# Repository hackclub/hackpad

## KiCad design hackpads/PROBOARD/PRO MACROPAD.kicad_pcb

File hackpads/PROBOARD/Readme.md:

# PROHACKBOARD
## My board is a simple and very much a standard macropad with 3 x 3 matrix with one encoder and one oled screen with xiao board and a case created in fusion 360

### Components
 . 9 switches
 . 1 encoder with switch
 . 1 oled 
 and in fusion 360 a backplate and joined main body and main plate with cavity for switches

 # images

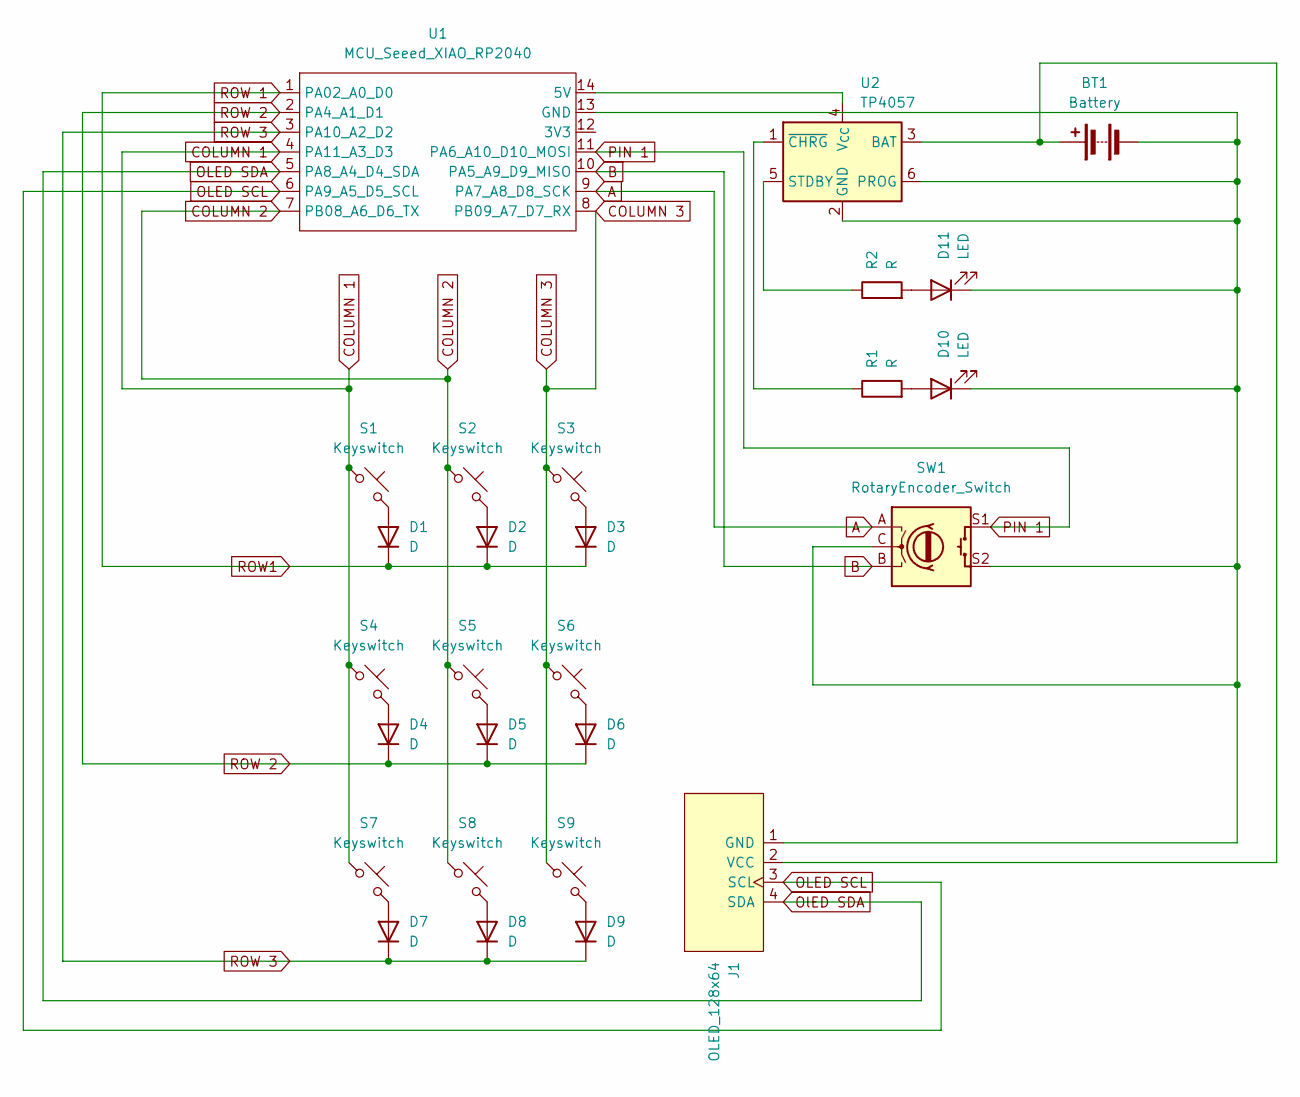
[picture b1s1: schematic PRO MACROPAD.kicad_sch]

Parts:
BT1: Battery; JST_PH_S2B-PH-K_1x02_P2.00mm_Horizontal
D1, D2, D3, D4, D5, D6, D7, D8, D9: D; Diode_SOD-123
D10, D11: LED; LED_D5.0mm
J1: OLED_128x64
R1, R2: R; Diode_SOD-123
S1, S2, S3, S4, S5, S6, S7, S8, S9: Keyswitch; Hotswap_MX_1.00u
SW1: RotaryEncoder_Switch; Encoder_EC11_MX_Combo
U1: MCU_Seeed_XIAO_RP2040; Seeed_XIAO_RP2040
U2: TP4057; TSOT-23-6

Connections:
A: SW1.A, U1.9 (PA7_A8_D8_SCK)
B: SW1.B, U1.10 (PA5_A9_D9_MISO)
COLUMN 1: S1.1, S4.1, S7.1, U1.4 (PA11_A3_D3)
COLUMN 2: S2.1, S5.1, S8.1, U1.7 (PB08_A6_D6_TX)
COLUMN 3: S3.1, S6.1, S9.1, U1.8 (PB09_A7_D7_RX)
unnamed: BT1.1 (+), J1.2 (VCC), U2.3 (BAT)
unnamed: BT1.2 (-), D10.1 (K), D11.1 (K), J1.1 (GND), SW1.C, SW1.S2, U1.13 (GND), U2.2 (GND), U2.6 (PROG)
unnamed: D1.2 (A), S1.2
unnamed: D2.2 (A), S2.2
unnamed: D3.2 (A), S3.2
unnamed: D4.2 (A), S4.2
unnamed: D5.2 (A), S5.2
unnamed: D6.2 (A), S6.2
unnamed: D7.2 (A), S7.2
unnamed: D8.2 (A), S8.2
unnamed: D9.2 (A), S9.2
unnamed: D10.2 (A), R1.2
unnamed: D11.2 (A), R2.2
unnamed: U1.14 (5V), U2.4 (V_{CC})
unnamed: R2.1, U2.5 (STDBY)
unnamed: R1.1, U2.1 (~CHRG)
OLED SCL: J1.3 (SCL), U1.6 (PA9_A5_D5_SCL)
OLED SDA: J1.4 (SDA), U1.5 (PA8_A4_D4_SDA)
PIN 1: SW1.S1, U1.11 (PA6_A10_D10_MOSI)
ROW 1: D1.1 (K), D2.1 (K), D3.1 (K), U1.1 (PA02_A0_D0)
ROW 2: D4.1 (K), D5.1 (K), D6.1 (K), U1.2 (PA4_A1_D1)
ROW 3: D7.1 (K), D8.1 (K), D9.1 (K), U1.3 (PA10_A2_D2)

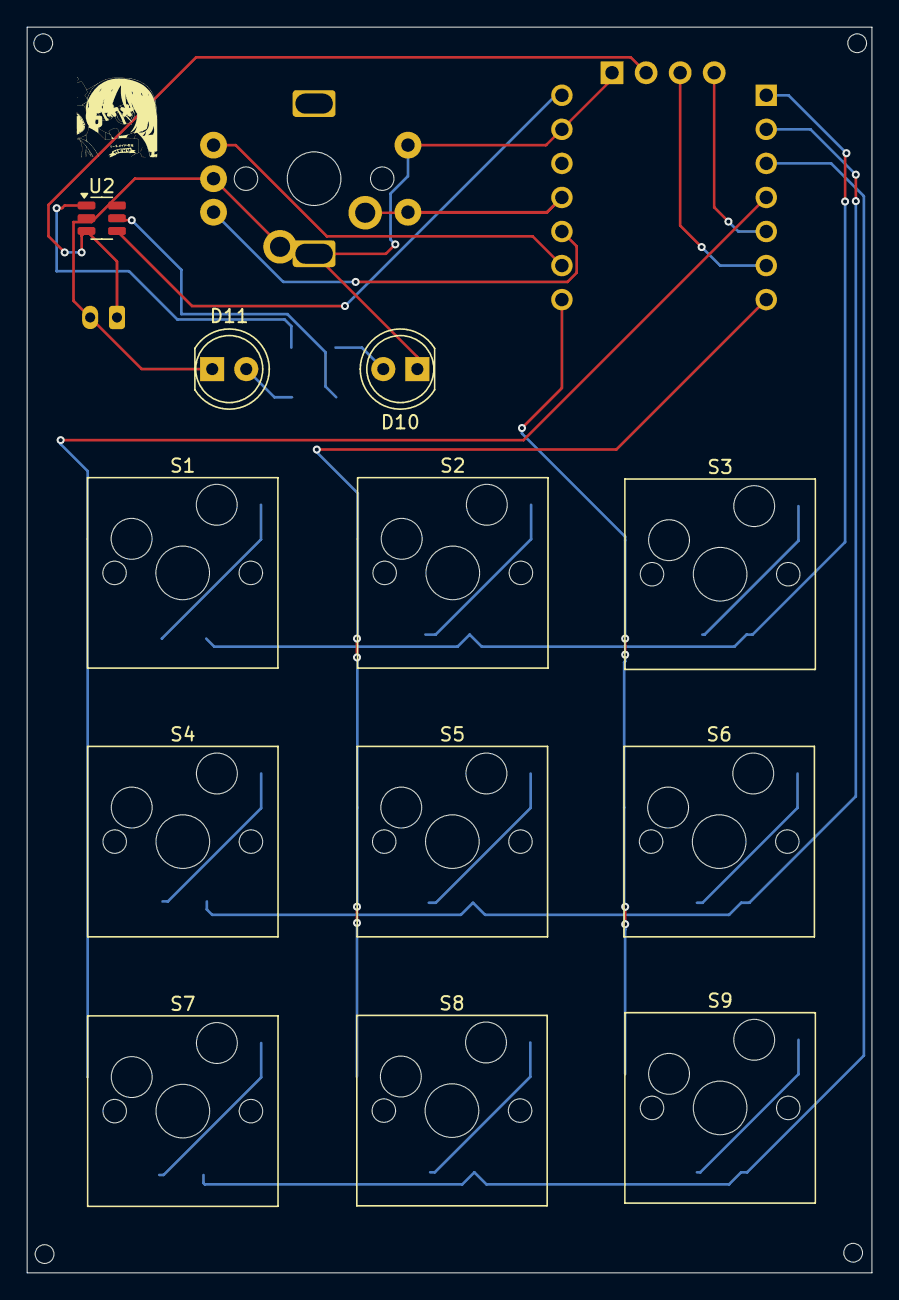
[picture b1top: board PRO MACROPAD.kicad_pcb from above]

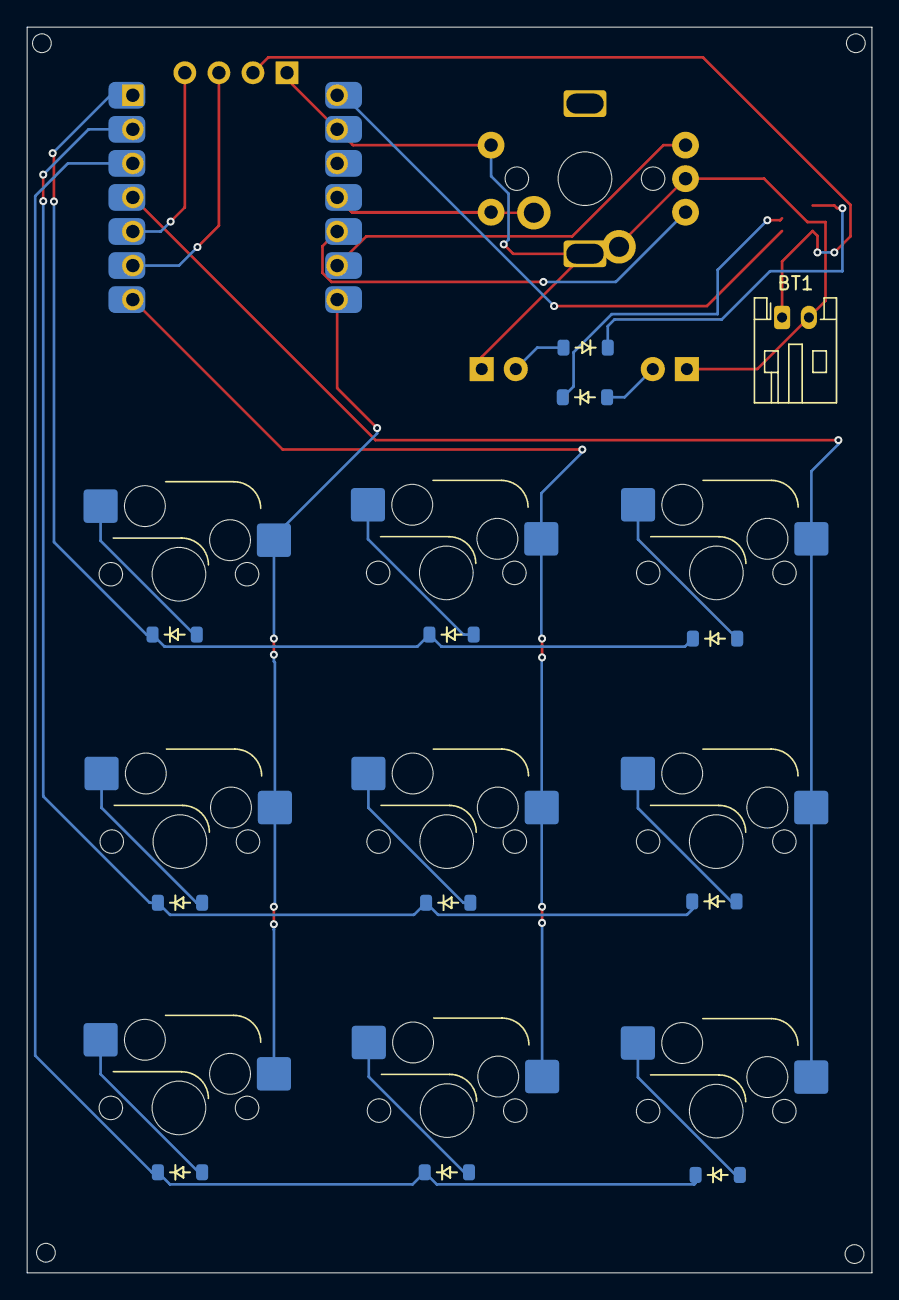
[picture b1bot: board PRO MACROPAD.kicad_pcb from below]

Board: 2 copper layers, 63.0 x 92.9 mm, 27 parts (13 on the bottom side), 27 nets.

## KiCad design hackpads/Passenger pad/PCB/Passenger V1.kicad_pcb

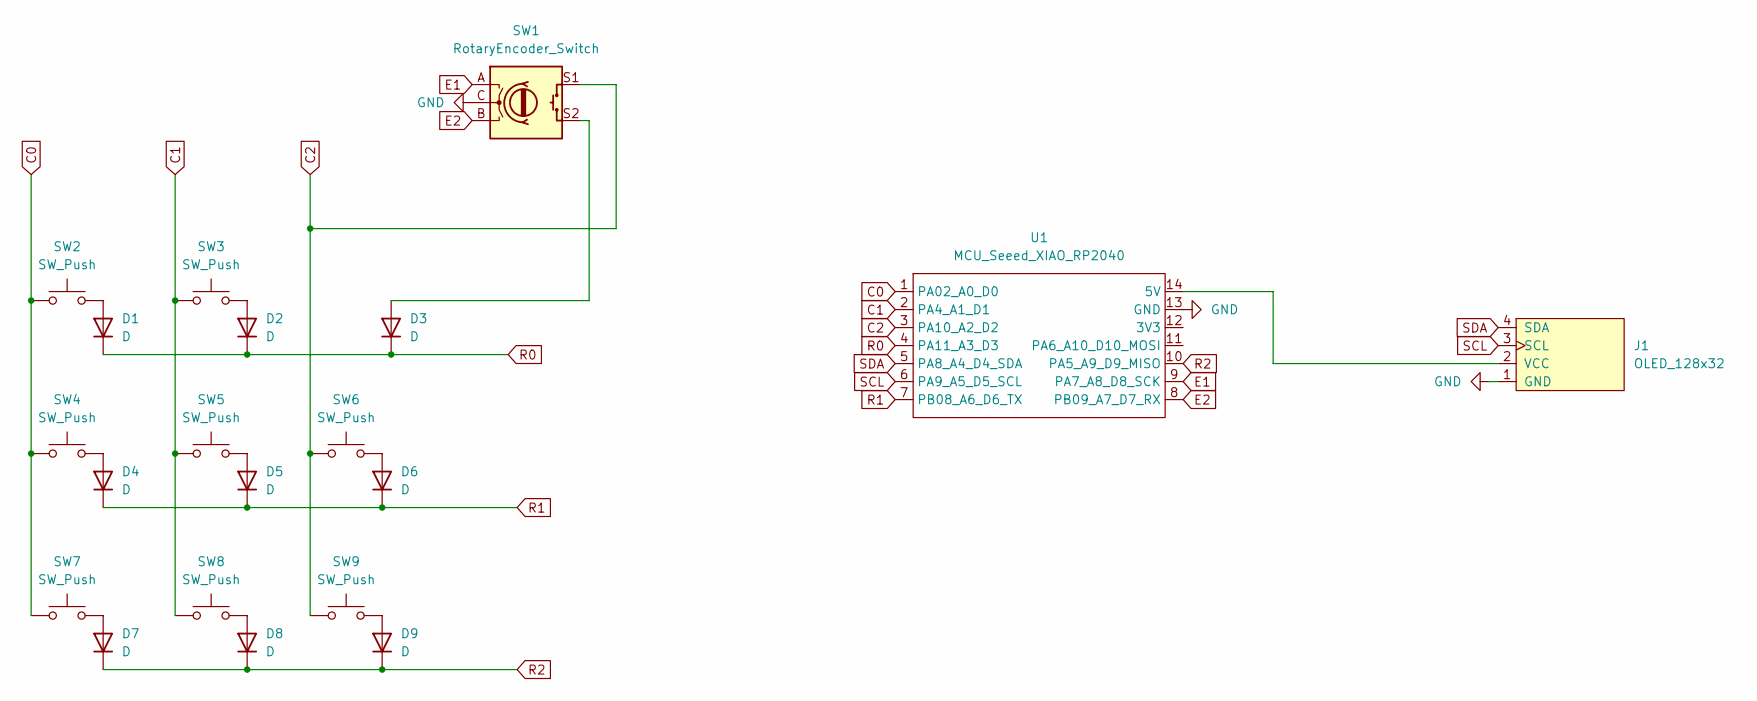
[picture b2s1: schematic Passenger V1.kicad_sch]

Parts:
D1, D2, D3, D4, D5, D6, D7, D8, D9: D; D_DO-35_SOD27_P7.62mm_Horizontal
J1: OLED_128x32; SSD1306-0.91-OLED-4pin-128x32 (2)
SW1: RotaryEncoder_Switch; RotaryEncoder_Alps_EC11E-Switch_Vertical_H20mm_CircularMoun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
SW2, SW3, SW4, SW5, SW6, SW7, SW8, SW9: SW_Push; SW_Cherry_MX_1.00u_PCB
U1: MCU_Seeed_XIAO_RP2040; XIAO-RP2040-DIP

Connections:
C0: SW2.1, SW4.1, SW7.1, U1.1 (PA02_A0_D0)
C1: SW3.1, SW5.1, SW8.1, U1.2 (PA4_A1_D1)
C2: SW1.S1, SW6.1, SW9.1, U1.3 (PA10_A2_D2)
E1: SW1.A, U1.9 (PA7_A8_D8_SCK)
E2: SW1.B, U1.8 (PB09_A7_D7_RX)
GND: J1.1 (GND), SW1.C, U1.13 (GND)
unnamed: D1.2 (A), SW2.2
unnamed: D2.2 (A), SW3.2
unnamed: D3.2 (A), SW1.S2
unnamed: D4.2 (A), SW4.2
unnamed: D5.2 (A), SW5.2
unnamed: D6.2 (A), SW6.2
unnamed: D7.2 (A), SW7.2
unnamed: D8.2 (A), SW8.2
unnamed: D9.2 (A), SW9.2
unnamed: J1.2 (VCC), U1.14 (5V)
R0: D1.1 (K), D2.1 (K), D3.1 (K), U1.4 (PA11_A3_D3)
R1: D4.1 (K), D5.1 (K), D6.1 (K), U1.7 (PB08_A6_D6_TX)
R2: D7.1 (K), D8.1 (K), D9.1 (K), U1.10 (PA5_A9_D9_MISO)
SCL: J1.3 (SCL), U1.6 (PA9_A5_D5_SCL)
SDA: J1.4 (SDA), U1.5 (PA8_A4_D4_SDA)

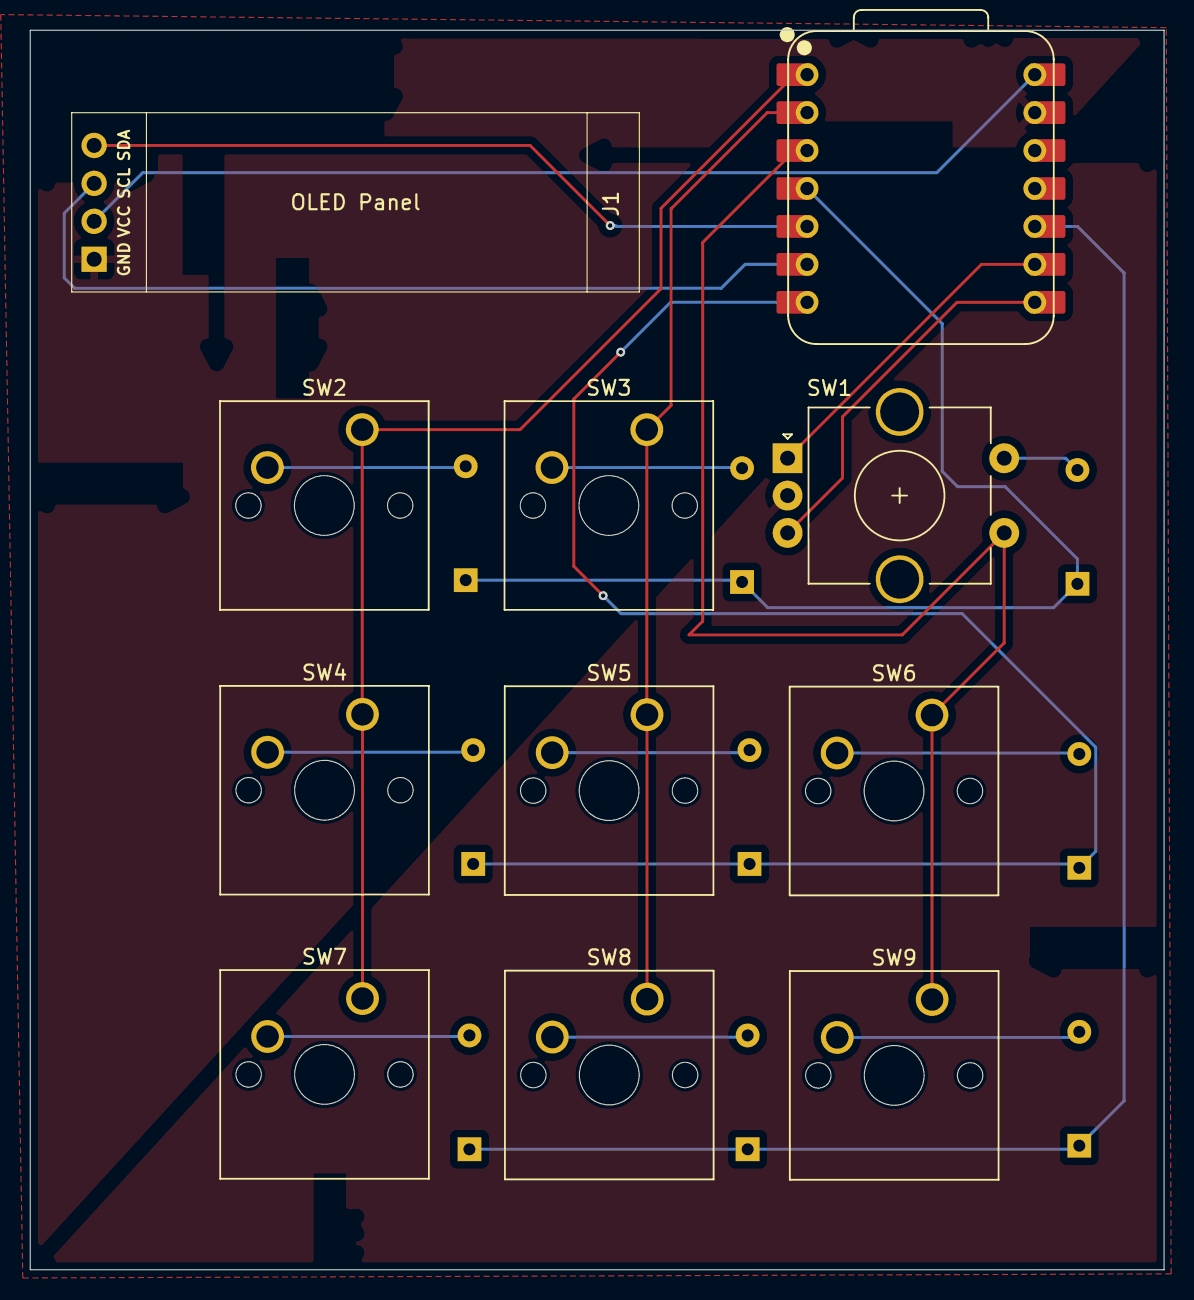
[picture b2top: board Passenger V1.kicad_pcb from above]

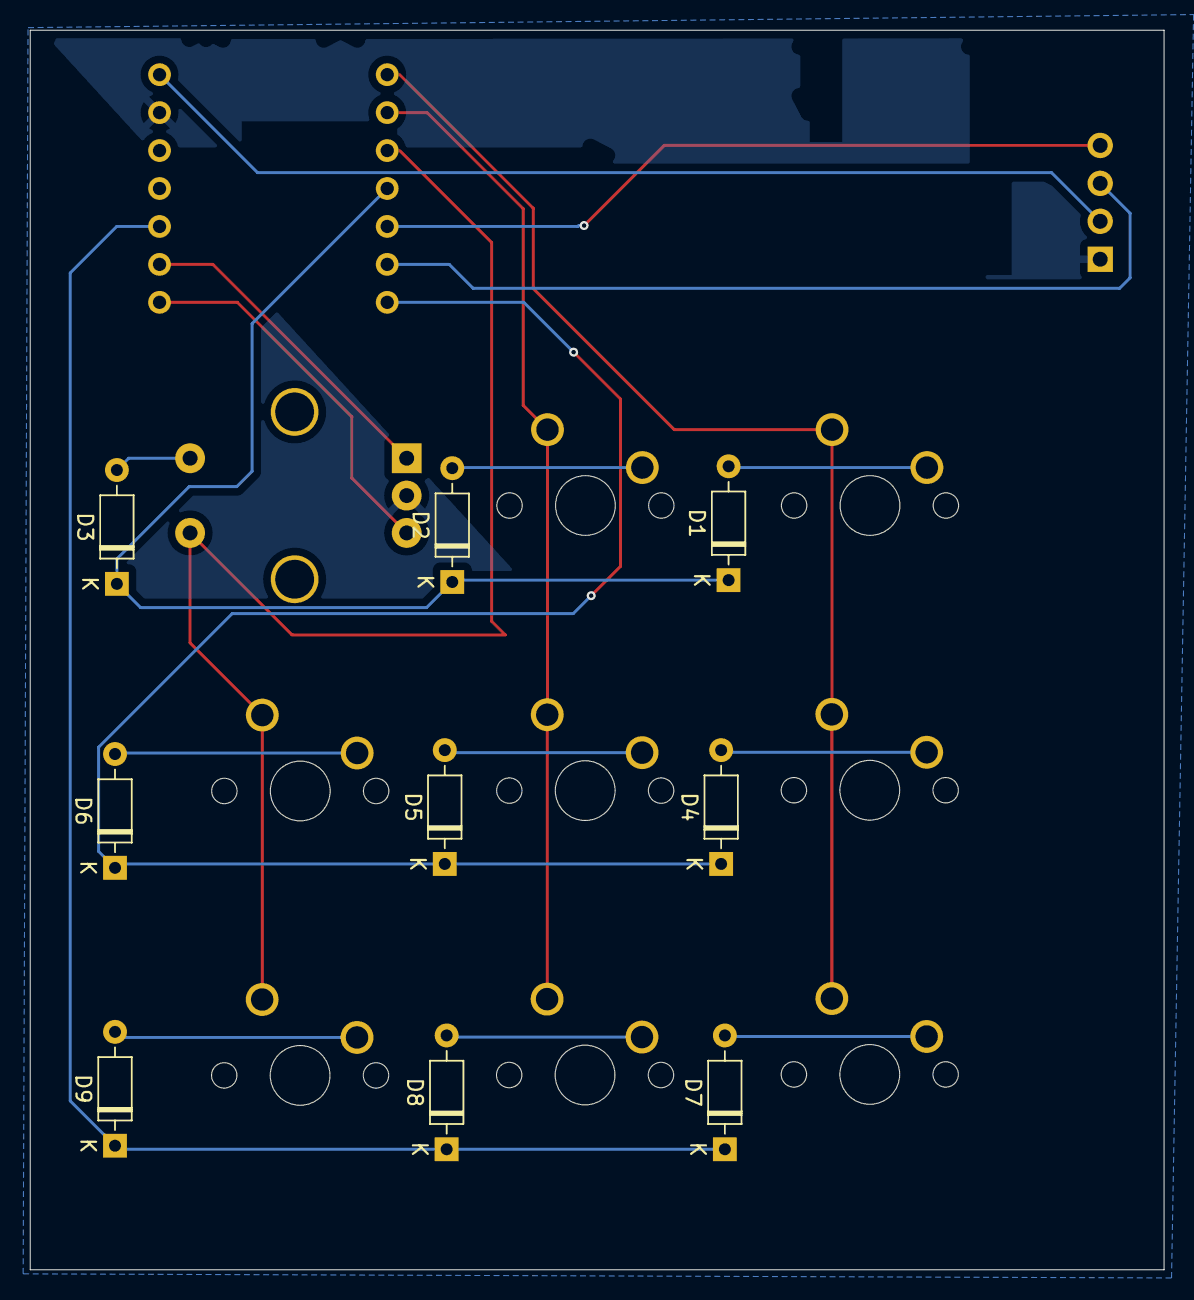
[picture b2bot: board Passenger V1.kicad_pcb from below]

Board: 2 copper layers, 75.9 x 83.0 mm, 20 parts (9 on the bottom side), 21 nets.

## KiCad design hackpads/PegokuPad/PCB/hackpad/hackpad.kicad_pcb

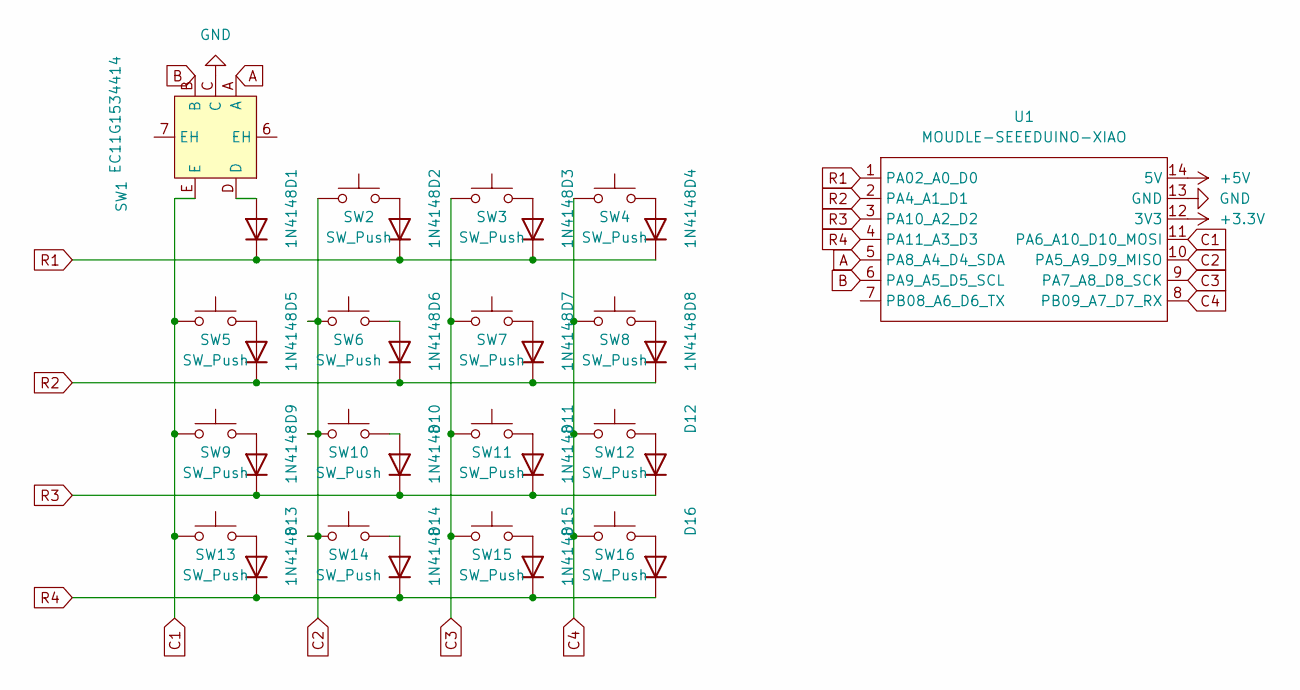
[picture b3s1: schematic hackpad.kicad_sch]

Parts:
D1, D2, D3, D4, D5, D6, D7, D8, D9, D10, D11, D12, D13, D14, D15, D16: 1N4148; D_DO-35_SOD27_P7.62mm_Horizontal
SW1: EC11G1534414; SW-TH_EC11G1534414; LCSC Part C1322547
SW2, SW3, SW4, SW5, SW6, SW7, SW8, SW9, SW10, SW11, SW12, SW13, SW14, SW15, SW16: SW_Push; SW_Cherry_MX_1.00u_PCB
U1: MOUDLE-SEEEDUINO-XIAO; XIAO-RP2040-DIP

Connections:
+3.3V: U1.12 (3V3)
+5V: U1.14 (5V)
A: SW1.A, U1.5 (PA8_A4_D4_SDA)
B: SW1.B, U1.6 (PA9_A5_D5_SCL)
C1: SW1.E, SW5.1, SW9.1, SW13.1, U1.11 (PA6_A10_D10_MOSI)
C2: SW2.1, SW6.1, SW10.1, SW14.1, U1.10 (PA5_A9_D9_MISO)
C3: SW3.1, SW7.1, SW11.1, SW15.1, U1.9 (PA7_A8_D8_SCK)
C4: SW4.1, SW8.1, SW12.1, SW16.1, U1.8 (PB09_A7_D7_RX)
GND: SW1.C, U1.13 (GND)
unnamed: D1.2 (A), SW1.D
unnamed: D2.2 (A), SW2.2
unnamed: D3.2 (A), SW3.2
unnamed: D4.2 (A), SW4.2
unnamed: D5.2 (A), SW5.2
unnamed: D6.2 (A), SW6.2
unnamed: D7.2 (A), SW7.2
unnamed: D8.2 (A), SW8.2
unnamed: D9.2 (A), SW9.2
unnamed: D10.2 (A), SW10.2
unnamed: D11.2 (A), SW11.2
unnamed: D12.2 (A), SW12.2
unnamed: D13.2 (A), SW13.2
unnamed: D14.2 (A), SW14.2
unnamed: D15.2 (A), SW15.2
unnamed: D16.2 (A), SW16.2
R1: D1.1 (K), D2.1 (K), D3.1 (K), D4.1 (K), U1.1 (PA02_A0_D0)
R2: D5.1 (K), D6.1 (K), D7.1 (K), D8.1 (K), U1.2 (PA4_A1_D1)
R3: D9.1 (K), D10.1 (K), D11.1 (K), D12.1 (K), U1.3 (PA10_A2_D2)
R4: D13.1 (K), D14.1 (K), D15.1 (K), D16.1 (K), U1.4 (PA11_A3_D3)

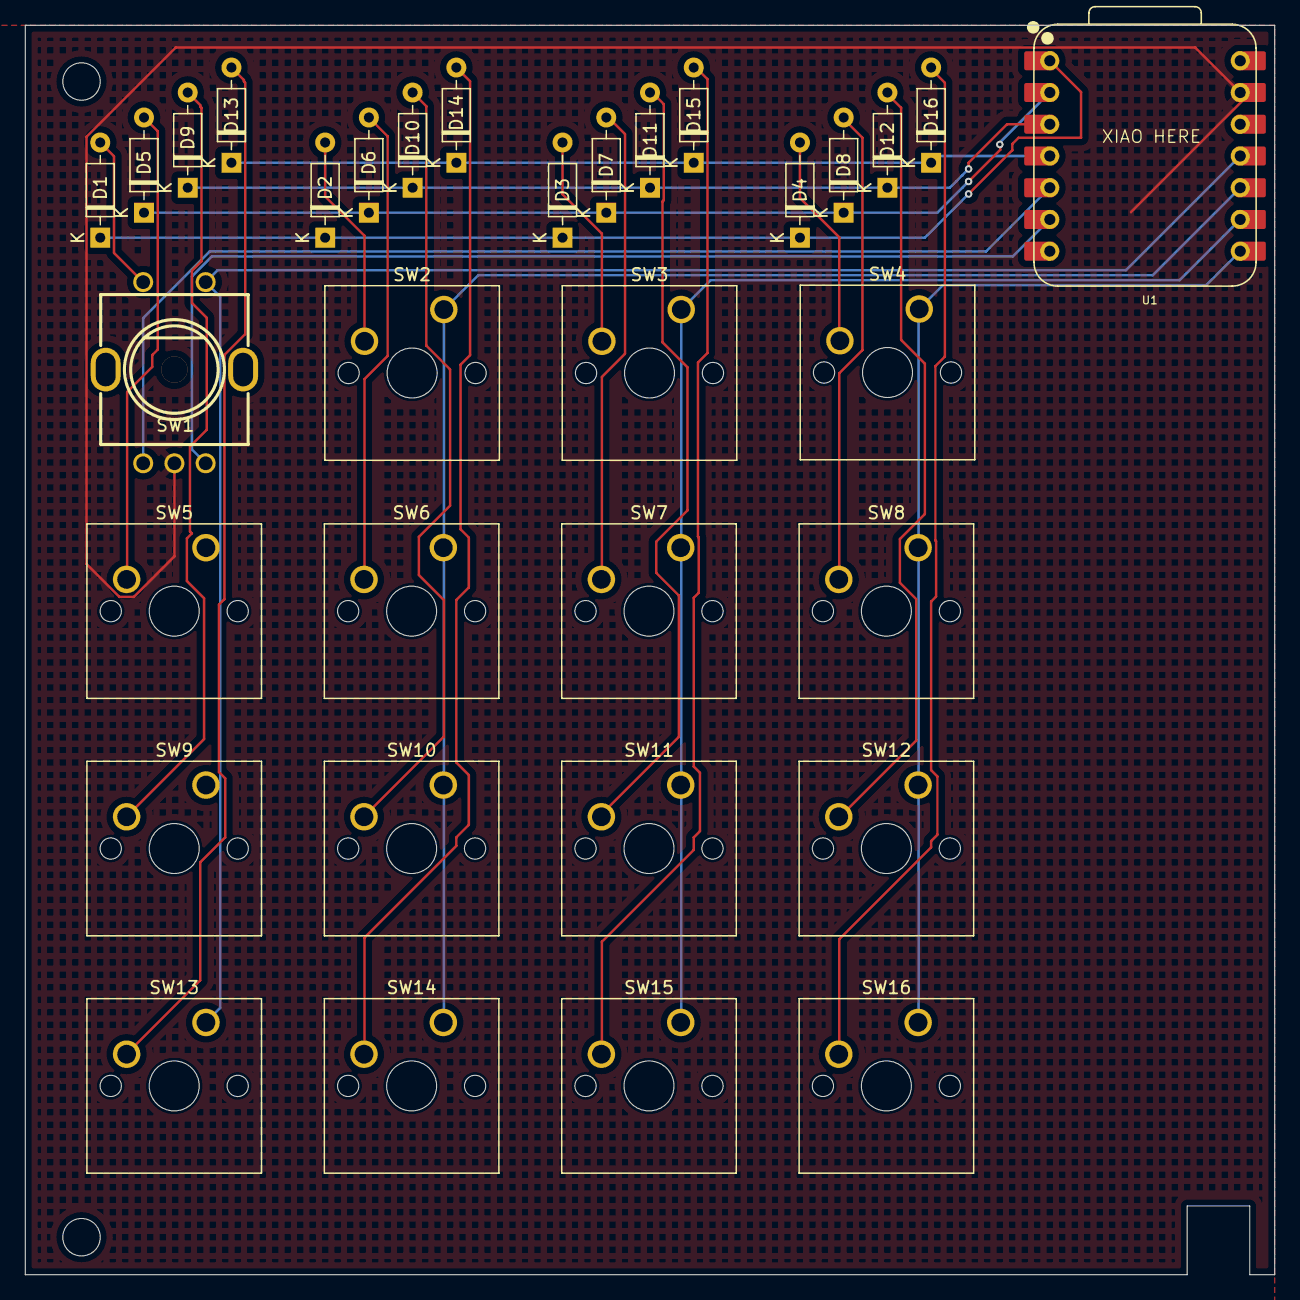
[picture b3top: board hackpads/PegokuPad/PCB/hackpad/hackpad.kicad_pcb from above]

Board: 2 copper layers, 100.0 x 100.0 mm, 33 parts (0 on the bottom side), 27 nets.

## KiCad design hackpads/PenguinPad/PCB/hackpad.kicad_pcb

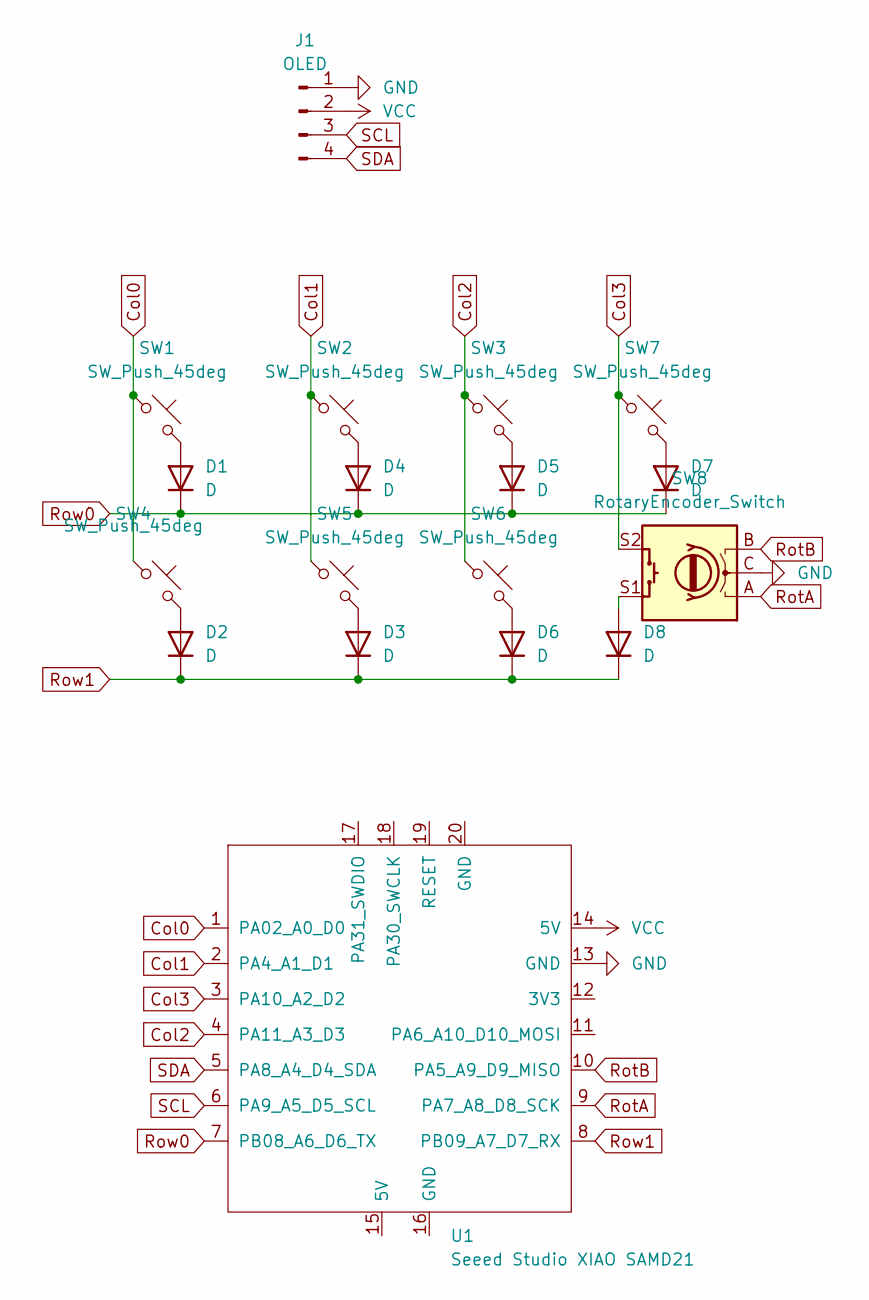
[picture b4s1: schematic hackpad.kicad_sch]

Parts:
D1, D2, D3, D4, D5, D6, D7, D8: D; D_DO-35_SOD27_P7.62mm_Horizontal
J1: OLED; SSD1306-0.91-OLED-4pin-128x32
SW1, SW2, SW3, SW4, SW5, SW6, SW7: SW_Push_45deg; SW_Cherry_MX_1.00u_PCB
SW8: RotaryEncoder_Switch; RotaryEncoder_Alps_EC11E-Switch_Vertical_H20mm
U1: Seeed Studio XIAO SAMD21; XIAO-Generic-Thruhole-14P-2.54-21X17.8MM

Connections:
Col0: SW1.1, SW4.1, U1.1 (PA02_A0_D0)
Col1: SW2.1, SW5.1, U1.2 (PA4_A1_D1)
Col2: SW3.1, SW6.1, U1.4 (PA11_A3_D3)
Col3: SW7.1, SW8.S2, U1.3 (PA10_A2_D2)
GND: J1.1, SW8.C, U1.13 (GND)
unnamed: D1.2 (A), SW1.2
unnamed: D2.2 (A), SW4.2
unnamed: D3.2 (A), SW5.2
unnamed: D4.2 (A), SW2.2
unnamed: D5.2 (A), SW3.2
unnamed: D6.2 (A), SW6.2
unnamed: D7.2 (A), SW7.2
unnamed: D8.2 (A), SW8.S1
RotA: SW8.A, U1.9 (PA7_A8_D8_SCK)
RotB: SW8.B, U1.10 (PA5_A9_D9_MISO)
Row0: D1.1 (K), D4.1 (K), D5.1 (K), D7.1 (K), U1.7 (PB08_A6_D6_TX)
Row1: D2.1 (K), D3.1 (K), D6.1 (K), D8.1 (K), U1.8 (PB09_A7_D7_RX)
SCL: J1.3, U1.6 (PA9_A5_D5_SCL)
SDA: J1.4, U1.5 (PA8_A4_D4_SDA)
VCC: J1.2, U1.14 (5V)

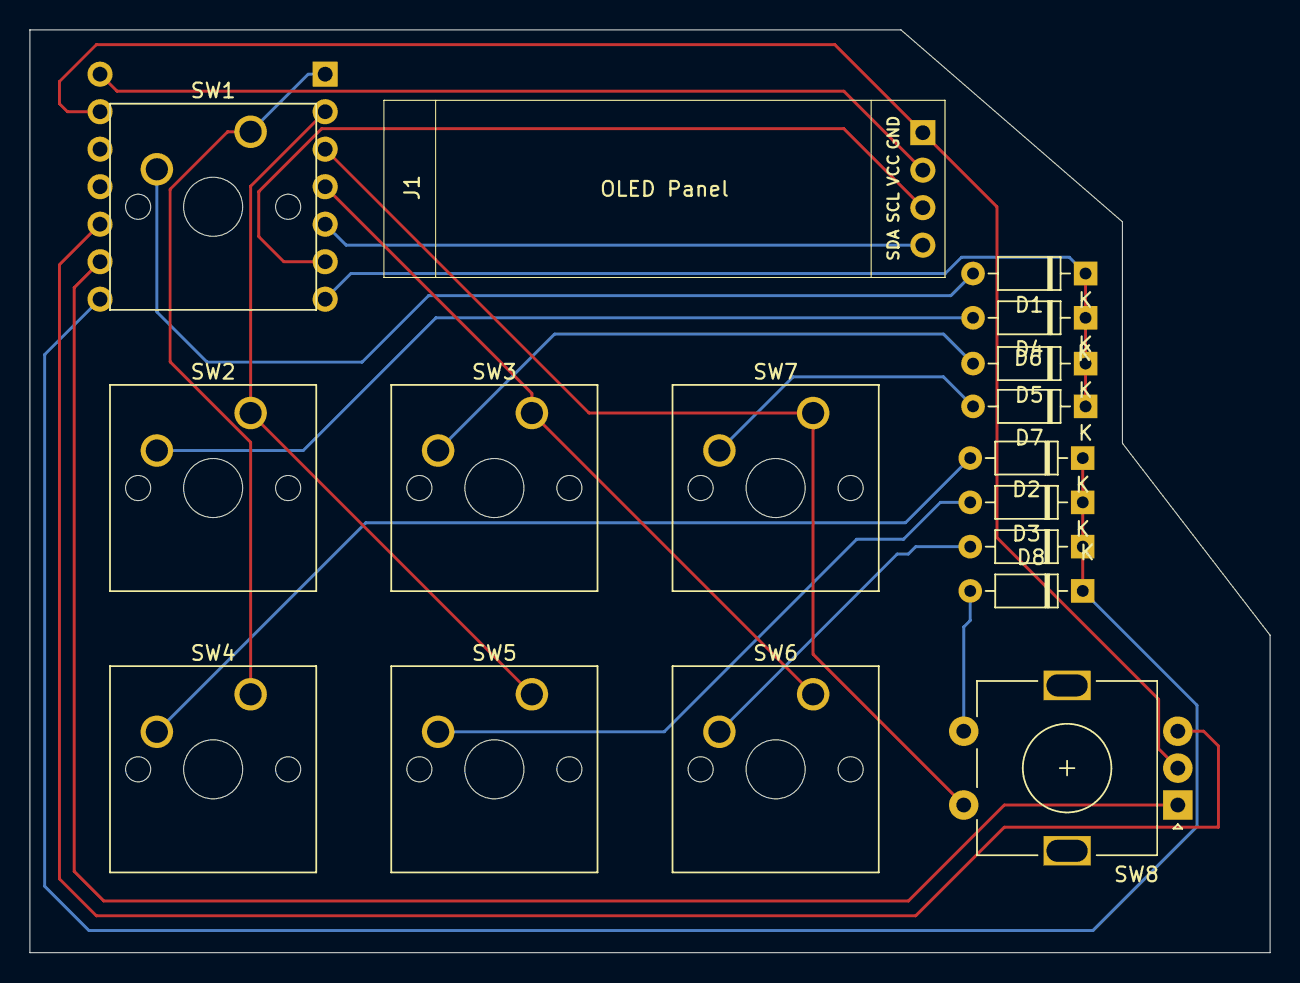
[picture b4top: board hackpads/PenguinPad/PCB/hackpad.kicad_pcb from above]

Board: 2 copper layers, 84.0 x 62.5 mm, 18 parts (1 on the bottom side), 20 nets.

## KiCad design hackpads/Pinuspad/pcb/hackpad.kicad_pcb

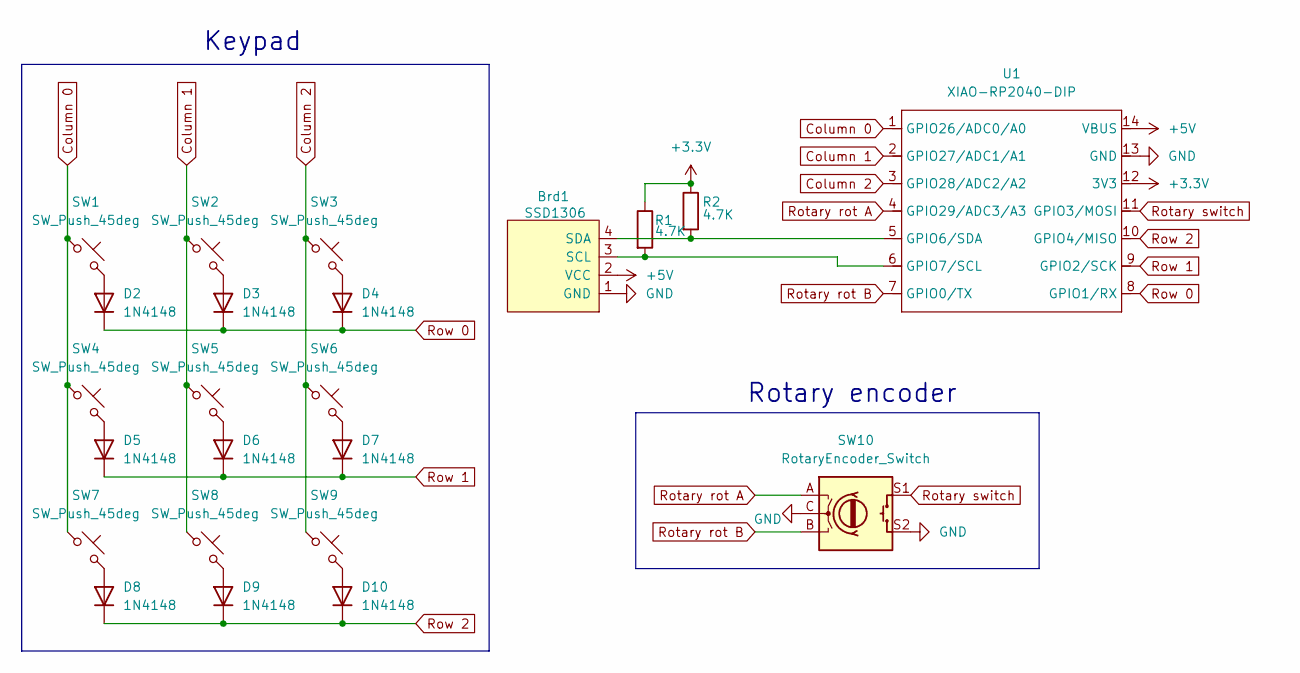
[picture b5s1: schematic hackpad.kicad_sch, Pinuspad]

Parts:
Brd1: SSD1306; 128x64OLED
D2, D3, D4, D5, D6, D7, D8, D9, D10: 1N4148; D_DO-35_SOD27_P7.62mm_Horizontal
R1, R2: 4.7K; R_Axial_DIN0204_L3.6mm_D1.6mm_P7.62mm_Horizontal
SW1, SW2, SW3, SW4, SW5, SW6, SW7, SW8, SW9: SW_Push_45deg; SW_Cherry_MX_1.00u_PCB
SW10: RotaryEncoder_Switch; RotaryEncoder_Alps_EC11E-Switch_Vertical_H20mm_CircularMoun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
U1: XIAO-RP2040-DIP

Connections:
+3.3V: R1.1, R2.1, U1.12 (3V3)
+5V: Brd1.2 (VCC), U1.14 (VBUS)
Column 0: SW1.1, SW4.1, SW7.1, U1.1 (GPIO26/ADC0/A0)
Column 1: SW2.1, SW5.1, SW8.1, U1.2 (GPIO27/ADC1/A1)
Column 2: SW3.1, SW6.1, SW9.1, U1.3 (GPIO28/ADC2/A2)
GND: Brd1.1 (GND), SW10.C, SW10.S2, U1.13 (GND)
unnamed: Brd1.3 (SCL), R1.2, U1.6 (GPIO7/SCL)
unnamed: Brd1.4 (SDA), R2.2, U1.5 (GPIO6/SDA)
unnamed: D2.2 (A), SW1.2
unnamed: D3.2 (A), SW2.2
unnamed: D4.2 (A), SW3.2
unnamed: D5.2 (A), SW4.2
unnamed: D6.2 (A), SW5.2
unnamed: D7.2 (A), SW6.2
unnamed: D8.2 (A), SW7.2
unnamed: D9.2 (A), SW8.2
unnamed: D10.2 (A), SW9.2
Rotary rot A: SW10.A, U1.4 (GPIO29/ADC3/A3)
Rotary rot B: SW10.B, U1.7 (GPIO0/TX)
Rotary switch: SW10.S1, U1.11 (GPIO3/MOSI)
Row 0: D2.1 (K), D3.1 (K), D4.1 (K), U1.8 (GPIO1/RX)
Row 1: D5.1 (K), D6.1 (K), D7.1 (K), U1.9 (GPIO2/SCK)
Row 2: D8.1 (K), D9.1 (K), D10.1 (K), U1.10 (GPIO4/MISO)

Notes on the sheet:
Rotary encoder
Keypad

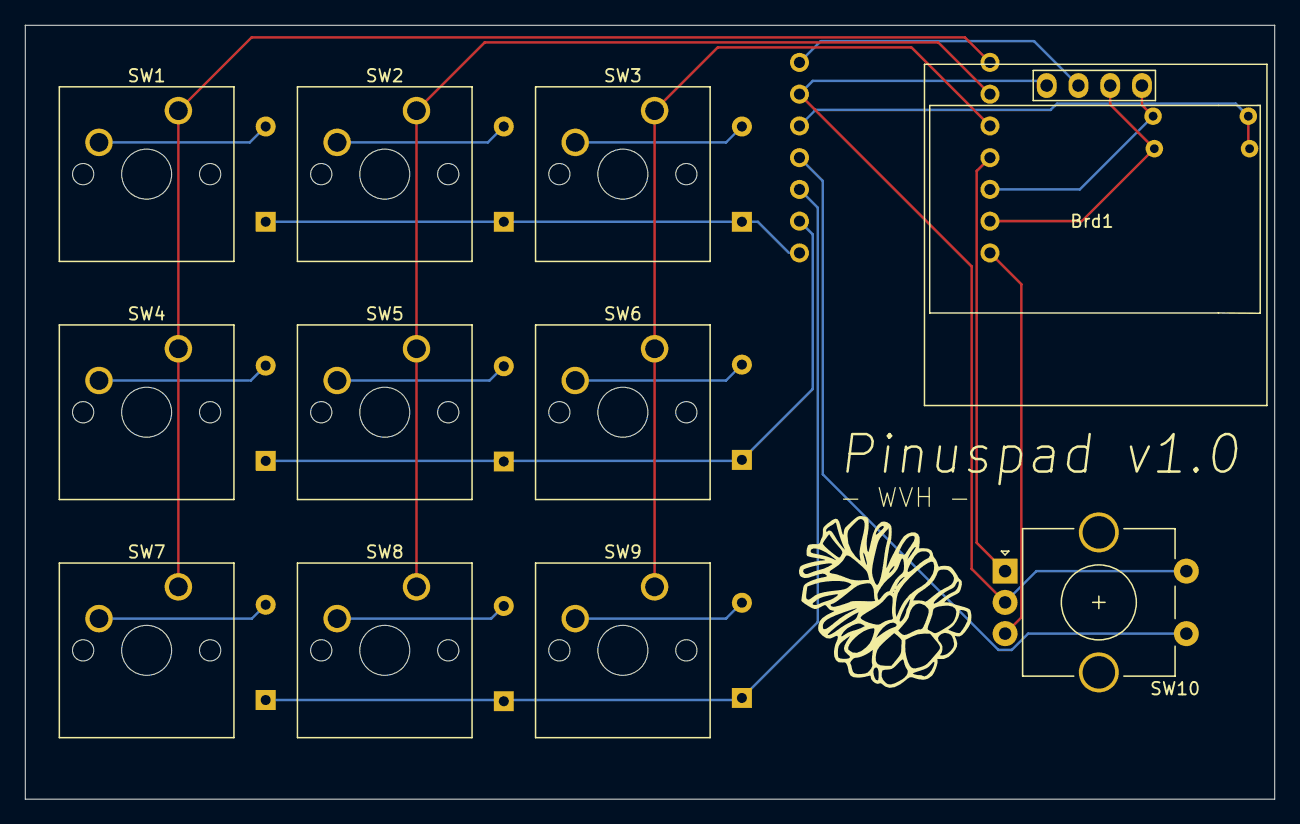
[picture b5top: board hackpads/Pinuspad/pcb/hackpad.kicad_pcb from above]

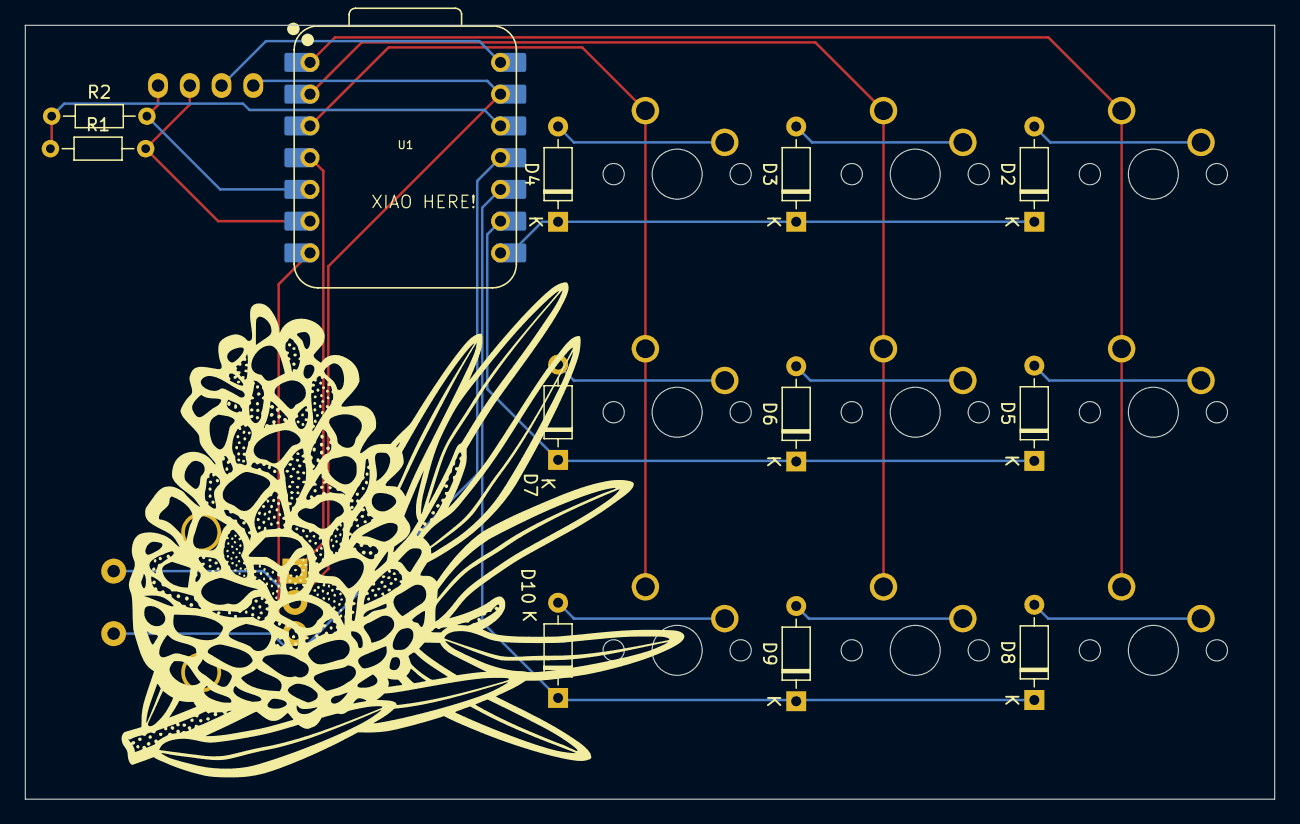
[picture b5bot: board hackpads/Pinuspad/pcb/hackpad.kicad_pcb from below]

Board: 2 copper layers, 100.0 x 61.9 mm, 23 parts (12 on the bottom side), 23 nets.

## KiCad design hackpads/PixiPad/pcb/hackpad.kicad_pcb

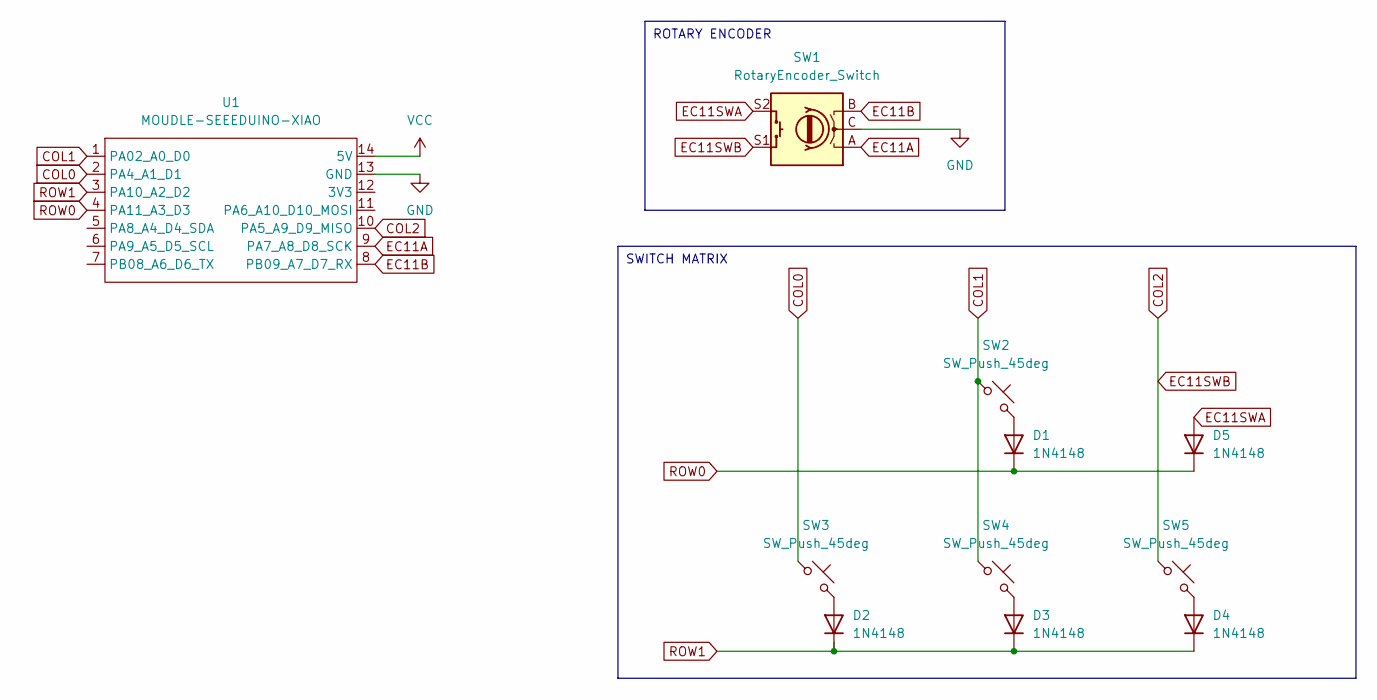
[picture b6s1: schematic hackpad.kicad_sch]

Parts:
D1, D2, D3, D4, D5: 1N4148; D_DO-35_SOD27_P7.62mm_Horizontal
SW1: RotaryEncoder_Switch; RotaryEncoder_Alps_EC11E-Switch_Vertical_H20mm
SW2, SW3, SW4, SW5: SW_Push_45deg; SW_Cherry_MX_1.00u_PCB
U1: MOUDLE-SEEEDUINO-XIAO; XIAO-Generic-Hybrid-14P-2.54-21X17.8MM

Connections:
COL0: SW3.1, U1.2 (PA4_A1_D1)
COL1: SW2.1, SW4.1, U1.1 (PA02_A0_D0)
COL2: SW1.S1, SW5.1, U1.10 (PA5_A9_D9_MISO)
EC11A: SW1.A, U1.9 (PA7_A8_D8_SCK)
EC11B: SW1.B, U1.8 (PB09_A7_D7_RX)
EC11SWA: D5.2 (A), SW1.S2
GND: SW1.C, U1.13 (GND)
unnamed: D1.2 (A), SW2.2
unnamed: D2.2 (A), SW3.2
unnamed: D3.2 (A), SW4.2
unnamed: D4.2 (A), SW5.2
ROW0: D1.1 (K), D5.1 (K), U1.4 (PA11_A3_D3)
ROW1: D2.1 (K), D3.1 (K), D4.1 (K), U1.3 (PA10_A2_D2)
VCC: U1.14 (5V)

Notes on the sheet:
ROTARY ENCODER
SWITCH MATRIX
